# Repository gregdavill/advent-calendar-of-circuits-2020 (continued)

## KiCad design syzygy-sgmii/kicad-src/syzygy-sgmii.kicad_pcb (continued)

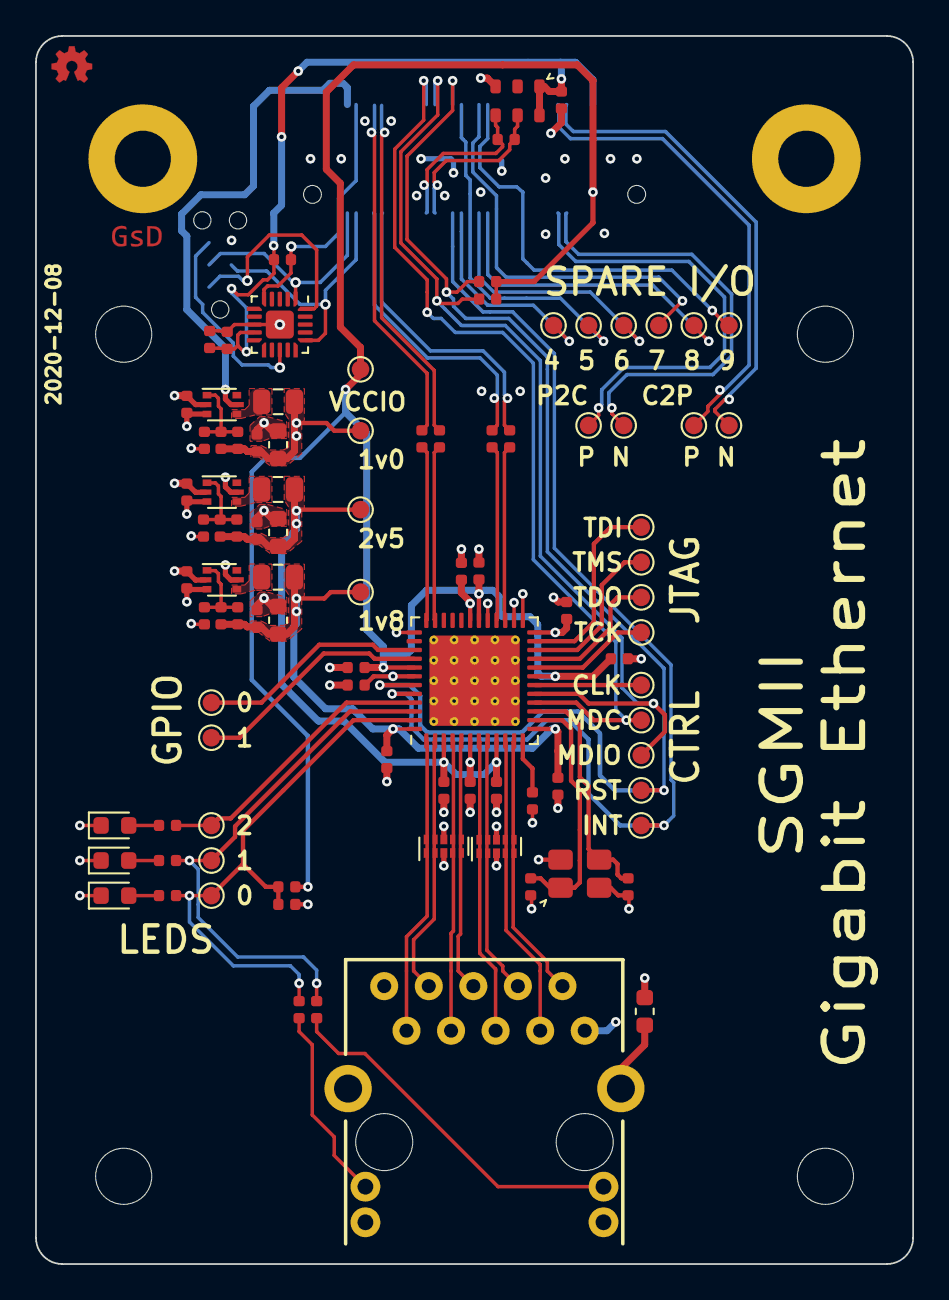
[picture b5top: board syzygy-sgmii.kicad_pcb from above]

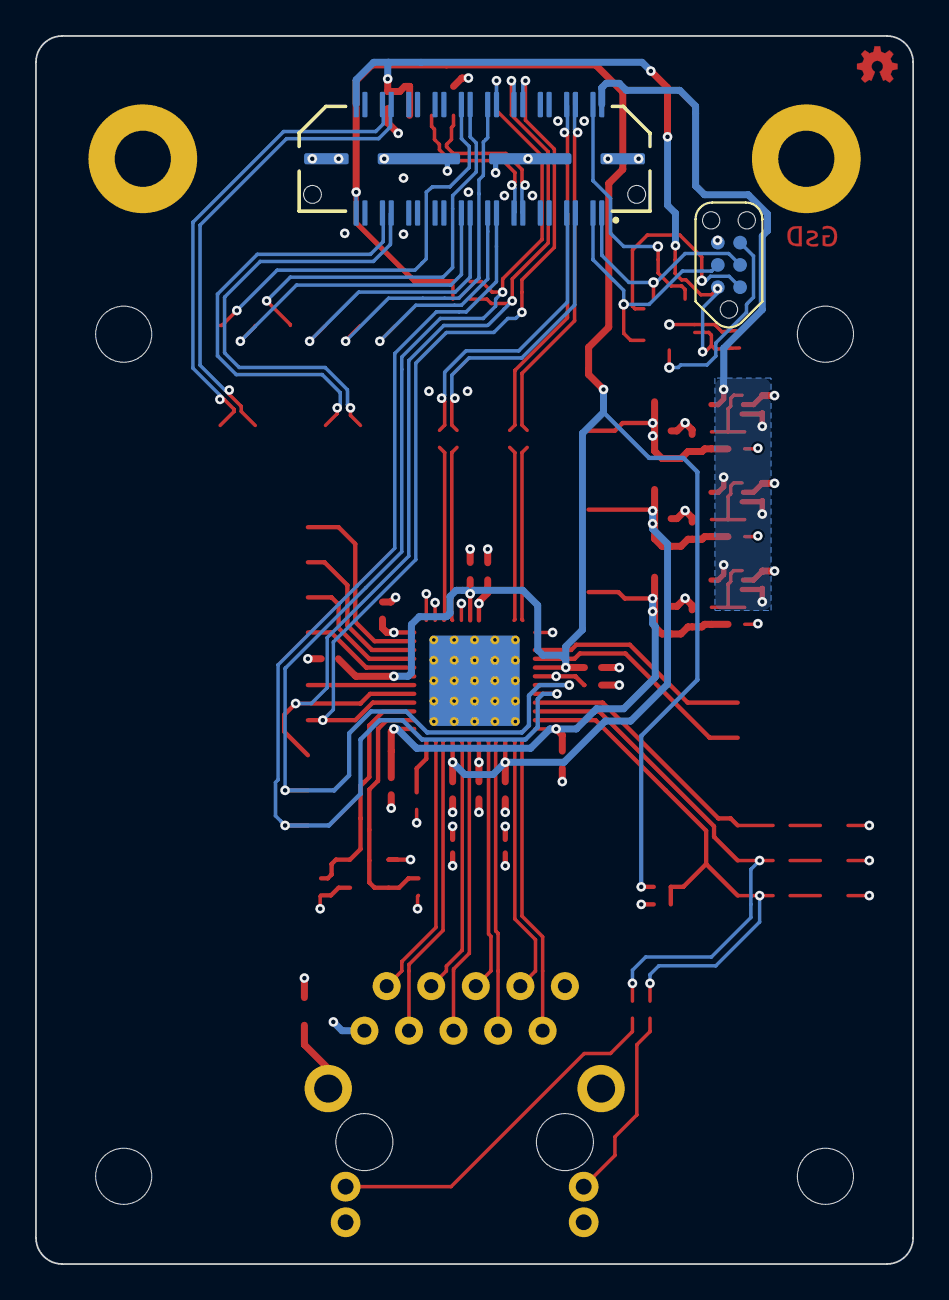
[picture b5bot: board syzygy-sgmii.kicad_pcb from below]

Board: 4 copper layers, 50.0 x 70.0 mm, 101 parts (2 on the bottom side), 69 nets.

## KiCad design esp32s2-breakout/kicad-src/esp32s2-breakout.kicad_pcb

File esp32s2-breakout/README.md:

# ESP32s2 Breakout

---

## What is it

ESP32S2 + Sharp memory LCD + prototyping area

## Folder structure

```
kicad-src: KiCad v6 source files
production:
 - Gerbers:      [project]_gerbers.zip
 - Schematic:    [project].pdf
 - Board render: [project].png
```

## Render

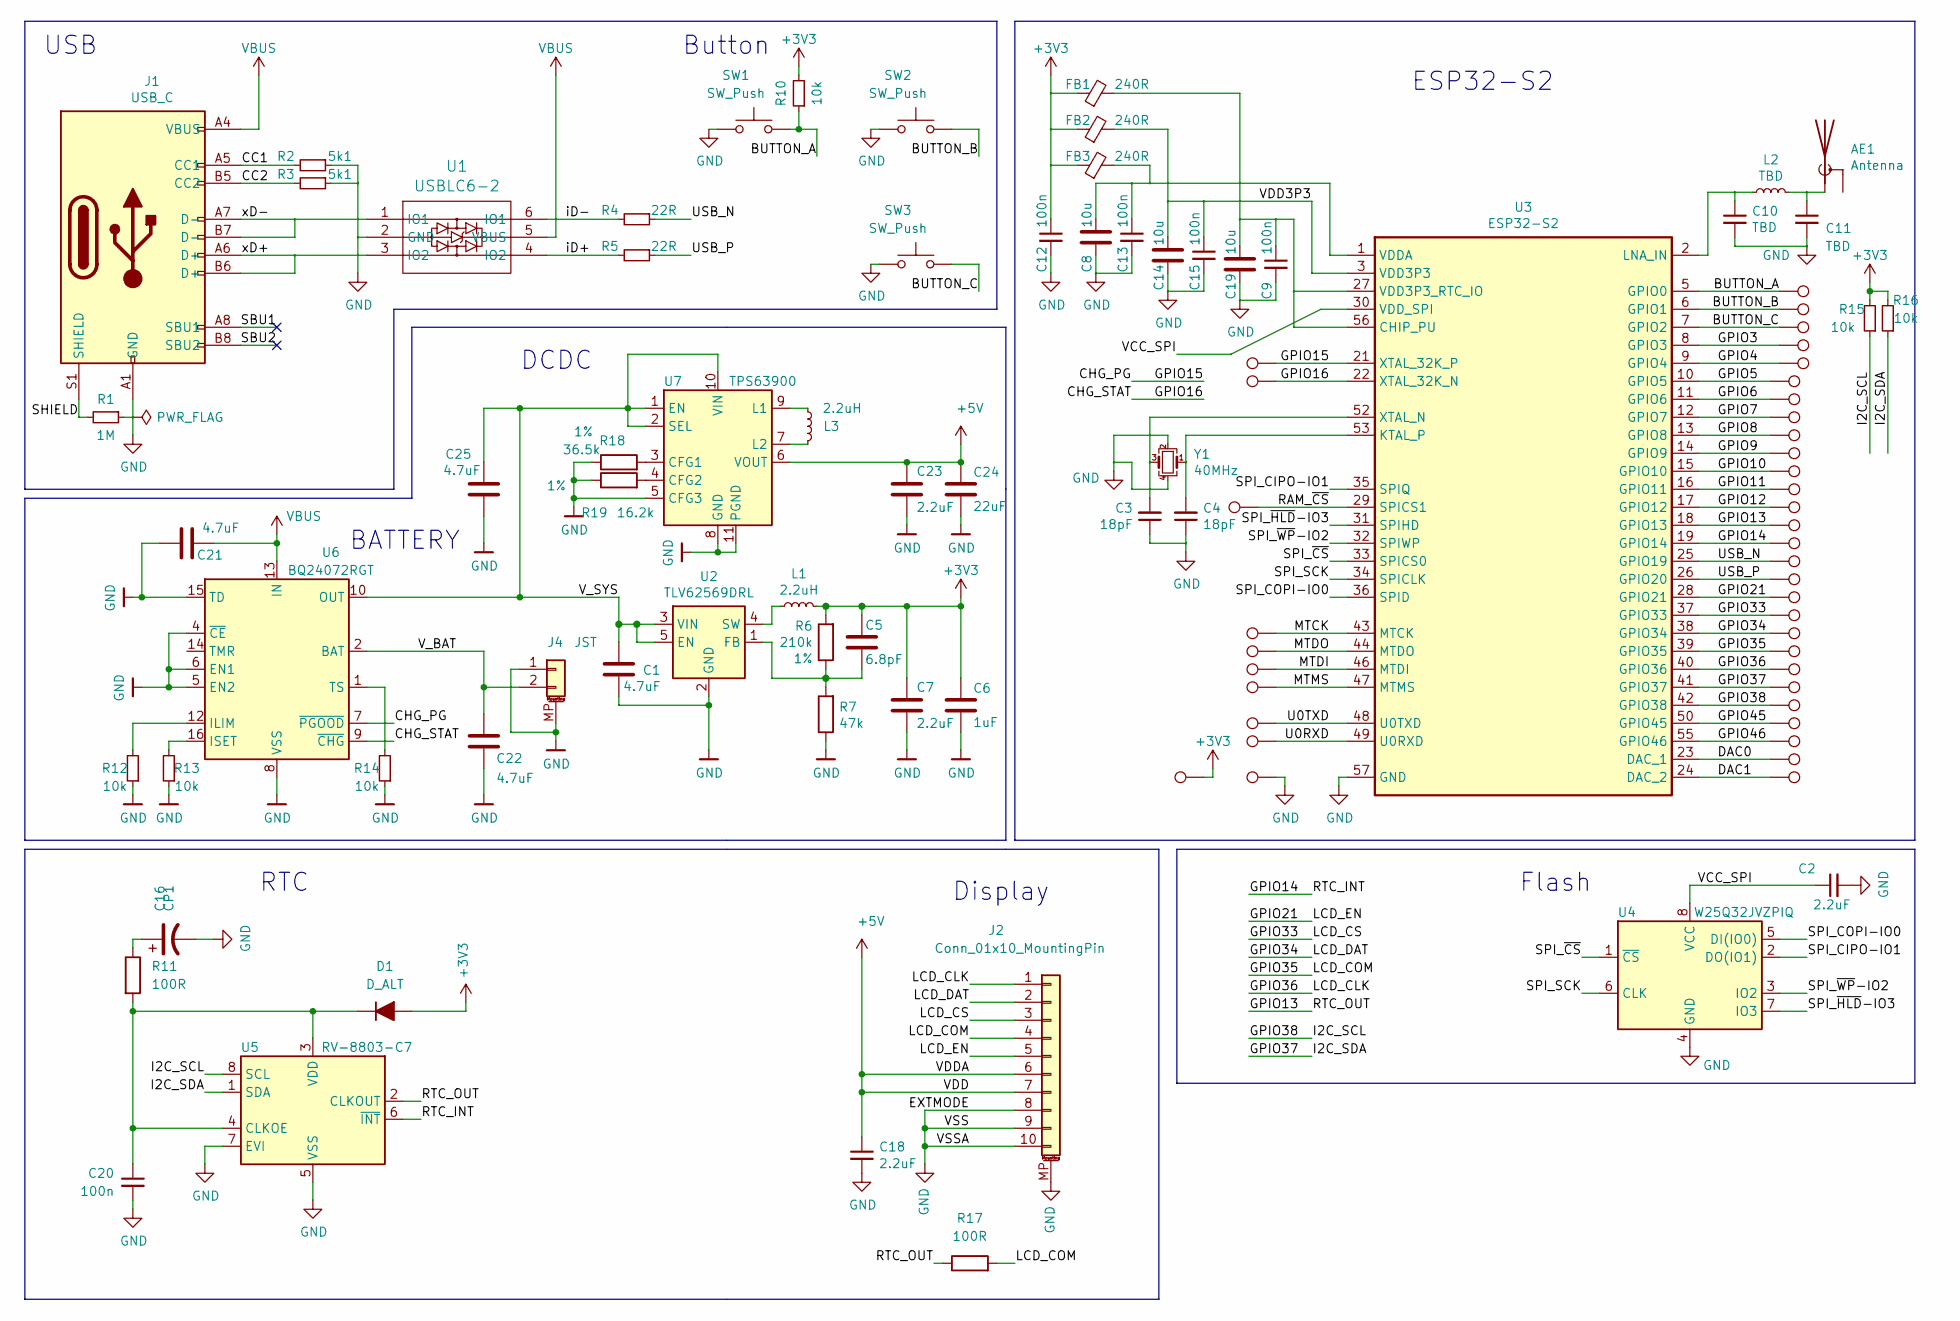
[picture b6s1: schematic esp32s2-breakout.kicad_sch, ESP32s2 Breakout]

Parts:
AE1: Antenna; Ant_3216
C1, C21, C22, C25: 4.7uF; C_0402_1005Metric
C2, C7, C18, C23: 2.2uF; C_0402_1005Metric
C3, C4: 18pF; C_0402_1005Metric
C5: 6.8pF; C_0402_1005Metric
C6: 1uF; C_0402_1005Metric
C8, C14, C19: 10u; C_0603_1608Metric
C9, C12, C13, C15, C20: 100n; C_0402_1005Metric
C10, C11: TBD; C_0402_1005Metric
C16: CP1; BatteryHolder_Seiko_MS621F
C24: 22uF; C_0603_1608Metric
D1: D_ALT; D_SOD-523
FB1, FB2, FB3: 240R; L_0402_1005Metric
J1: USB_C; USB_C_Receptacle_HRO_TYPE-C-31-M-12
J2: Conn_01x10_MountingPin; Hirose_FH33-10S-0.5SH_1x10-1MP_P0.50mm_Horizontal
J4: JST; BM02B-GHS-TBT
L1, L3: 2.2uH; L_0805_2012Metric
L2: TBD; L_0402_1005Metric
R1: 1M; R_0402_1005Metric
R2, R3: 5k1; R_0402_1005Metric
R4, R5: 22R; R_0402_1005Metric
R6: 210k; R_0402_1005Metric
R7: 47k; R_0402_1005Metric
R10, R12, R13, R14, R15, R16: 10k; R_0402_1005Metric
R11, R17: 100R; R_0402_1005Metric
R18: 36.5k; R_0402_1005Metric
R19: 16.2k; R_0402_1005Metric
SW1, SW2, SW3: SW_Push; SW_SPST_PTS810
TP1, TP2, TP3, TP4, TP5, TP6, TP7, TP8, TP9, TP10, TP11, TP12, TP13, TP14, TP15, TP16, TP17, TP18, TP19, TP20, TP21, TP22, TP23, TP24, TP25, TP26, TP27, TP28, TP29, TP30, TP31, TP32, TP33, TP34, TP35, TP36, TP37, TP38, TP39: TestPoint; TestPoint_Pad_1.0x1.0mm
U1: USBLC6-2; SOT-666
U2: TLV62569DRL; SOT-666
U3: ESP32-S2; QFN-56-1EP_7x7mm_P0.4mm_EP5.6x5.6mm
U4: W25Q32JVZPIQ; WSON-8-1EP_6x5mm_P1.27mm_EP3.4x4mm
U5: RV-8803-C7; RTC_SMD_MicroCrystal_C3_2.5x3.7mm
U6: BQ24072RGT; VQFN-16-1EP_3x3mm_P0.5mm_EP1.6x1.6mm
U7: TPS63900; WSON-10-1EP_2.5x2.5mm_P0.5mm_EP1.2x2mm_ThermalVias
Y1: 40MHz; Crystal_SMD_4Pin_2.0x1.6mm

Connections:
+3V3: C5.1, C6.1, C7.1, C12.1, D1.2 (A), FB1.1, FB2.1, FB3.1, L1.2, R6.2, R10.2, R15.2, R16.2, TP39.1; also elsewhere on the board
+5V: C18.1, C23.1, C24.1, J2.6, J2.7, U7.6 (VOUT)
/BUTTON_A: R10.1, SW1.2, TP35.1, U3.5 (GPIO0)
/BUTTON_B: SW2.2, TP36.1, U3.6 (GPIO1)
/BUTTON_C: SW3.2, TP37.1, U3.7 (GPIO2)
/CC1: J1.A5 (CC1), R2.2
/CC2: J1.B5 (CC2), R3.2
/DAC0: TP31.1, U3.23 (DAC_1)
/DAC1: TP32.1, U3.24 (DAC_2)
/GPIO3: TP9.1, U3.8 (GPIO3)
/GPIO4: TP8.1, U3.9 (GPIO4)
/GPIO5: TP10.1, U3.10 (GPIO5)
/GPIO6: TP11.1, U3.11 (GPIO6)
/GPIO7: TP12.1, U3.12 (GPIO7)
/GPIO8: TP13.1, U3.13 (GPIO8)
/GPIO9: TP14.1, U3.14 (GPIO9)
/GPIO10: TP15.1, U3.15 (GPIO10)
/GPIO11: TP16.1, U3.16 (GPIO11)
/GPIO12: TP17.1, U3.17 (GPIO12)
/GPIO14: TP19.1, U3.19 (GPIO14), U5.6 (~INT)
/GPIO15: TP33.1, U3.21 (XTAL_32K_P), U6.7 (~PGOOD)
/GPIO16: TP34.1, U3.22 (XTAL_32K_N), U6.9 (~CHG)
/GPIO21: J2.5, TP22.1, U3.28 (GPIO21)
/GPIO33: J2.3, TP23.1, U3.37 (GPIO33)
/GPIO34: J2.2, TP24.1, U3.38 (GPIO34)
/GPIO35: J2.4, R17.2, TP25.1, U3.39 (GPIO35)
/GPIO36: J2.1, TP26.1, U3.40 (GPIO36)
/GPIO37: R16.1, TP27.1, U3.41 (GPIO37), U5.1 (SDA)
/GPIO38: R15.1, TP28.1, U3.42 (GPIO38), U5.8 (SCL)
/GPIO45: TP29.1, U3.50 (GPIO45)
/GPIO46: TP30.1, U3.55 (GPIO46)
/MTCK: TP1.1, U3.43 (MTCK)
/MTDI: TP3.1, U3.46 (MTDI)
/MTDO: TP2.1, U3.44 (MTDO)
/MTMS: TP4.1, U3.47 (MTMS)
/RAM_~CS: TP38.1, U3.29 (SPICS1)
/RTC_OUT: R17.1, TP18.1, U3.18 (GPIO13), U5.2 (CLKOUT)
/SBU1: J1.A8 (SBU1)
/SBU2: J1.B8 (SBU2)
/SHIELD: J1.S1 (SHIELD), R1.2
/SPI_CIPO-IO1: U3.35 (SPIQ), U4.2 (DO(IO1))
/SPI_COPI-IO0: U3.36 (SPID), U4.5 (DI(IO0))
/SPI_SCK: U3.34 (SPICLK), U4.6 (CLK)
/SPI_~CS: U3.33 (SPICS0), U4.1 (~CS)
/SPI_~HLD~-IO3: U3.31 (SPIHD), U4.7 (IO3)
/SPI_~WP~-IO2: U3.32 (SPIWP), U4.3 (IO2)
/U0RXD: TP6.1, U3.49 (U0RXD)
/U0TXD: TP5.1, U3.48 (U0TXD)
/USB_N: R4.1, TP20.1, U3.25 (GPIO19)
/USB_P: R5.1, TP21.1, U3.26 (GPIO20)
/VCC_SPI: C2.1, U3.30 (VDD_SPI), U4.8 (VCC)
/VDD3P3: C14.1, C15.1, FB2.2, U3.3 (VDD3P3), U3.4 (VDD3P3)
/V_BAT: C22.2, J4.2, U6.2 (BAT), U6.3 (BAT)
/V_SYS: C1.1, C25.1, U2.3 (VIN), U2.5 (EN), U6.10 (OUT), U6.11 (OUT), U7.1 (EN), U7.2 (SEL), U7.10 (VIN)
/iD+: R5.2, U1.4 (IO2)
/iD-: R4.2, U1.6 (IO1)
/xD+: J1.A6 (D+), J1.B6 (D+), U1.3 (IO2)
/xD-: J1.A7 (D-), J1.B7 (D-), U1.1 (IO1)
GND: C1.2, C2.2, C3.1, C4.1, C6.2, C7.2, C8.2, C9.2, C10.2, C11.2, C12.2, C13.2, C14.2, C15.2, C16.2, C18.2, C19.2, C20.2, C21.1, C22.1, C23.2, C24.2, C25.2, J1.A1 (GND), J1.A12 (GND), J1.B1 (GND), J1.B12 (GND), J2.8, J2.9, J2.10, J2.MP (MountPin), J4.1, J4.MP (MountPin), R1.1, R2.1, R3.1, R7.1, R12.1, R13.1, R14.1, R18.1, R19.1, SW1.1, SW2.1, SW3.1, TP7.1, U1.2 (GND), U2.2 (GND), U3.57 (GND), U4.4 (GND), U5.5 (VSS), U5.7 (EVI), U6.4 (~CE), U6.5 (EN2), U6.6 (EN1), U6.8 (VSS), U6.15 (TD), U6.17 (VSS), U7.5 (CFG3), U7.8 (GND), U7.11 (PGND), Y1.2, Y1.4; also elsewhere on the board
unnamed: AE1.1 (A), C11.1, L2.2
unnamed: C3.2, U3.52 (XTAL_N), Y1.3
unnamed: C4.2, U3.53 (KTAL_P), Y1.1
unnamed: C5.2, R6.1, R7.2, U2.1 (FB)
unnamed: C10.1, L2.1, U3.2 (LNA_IN)
unnamed: C8.1, C13.1, FB3.2, U3.1 (VDDA), U3.51 (VDDA), U3.54 (VDDA)
unnamed: C16.1, R11.1
unnamed: C9.1, C19.1, FB1.2, U3.20 (VDD3P3_RTC), U3.27 (VDD3P3_RTC_IO), U3.45 (VDD3P3_CPU), U3.56 (CHIP_PU)
unnamed: C20.1, D1.1 (K), R11.2, U5.3 (VDD), U5.4 (CLKOE)
unnamed: L1.1, U2.4 (SW)
unnamed: L3.1, U7.9 (L1)
unnamed: L3.2, U7.7 (L2)
unnamed: R12.2, U6.12 (ILIM)
unnamed: R13.2, U6.16 (ISET)
unnamed: R14.2, U6.1 (TS)
unnamed: R18.2, U7.3 (CFG1)
unnamed: R19.2, U7.4 (CFG2)
VBUS: C21.2, J1.A4 (VBUS), J1.A9 (VBUS), J1.B4 (VBUS), J1.B9 (VBUS), U1.5 (VBUS), U6.13 (IN)

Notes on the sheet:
USB
RTC
BATTERY
DCDC
Button
Display
ESP32-S2
Flash

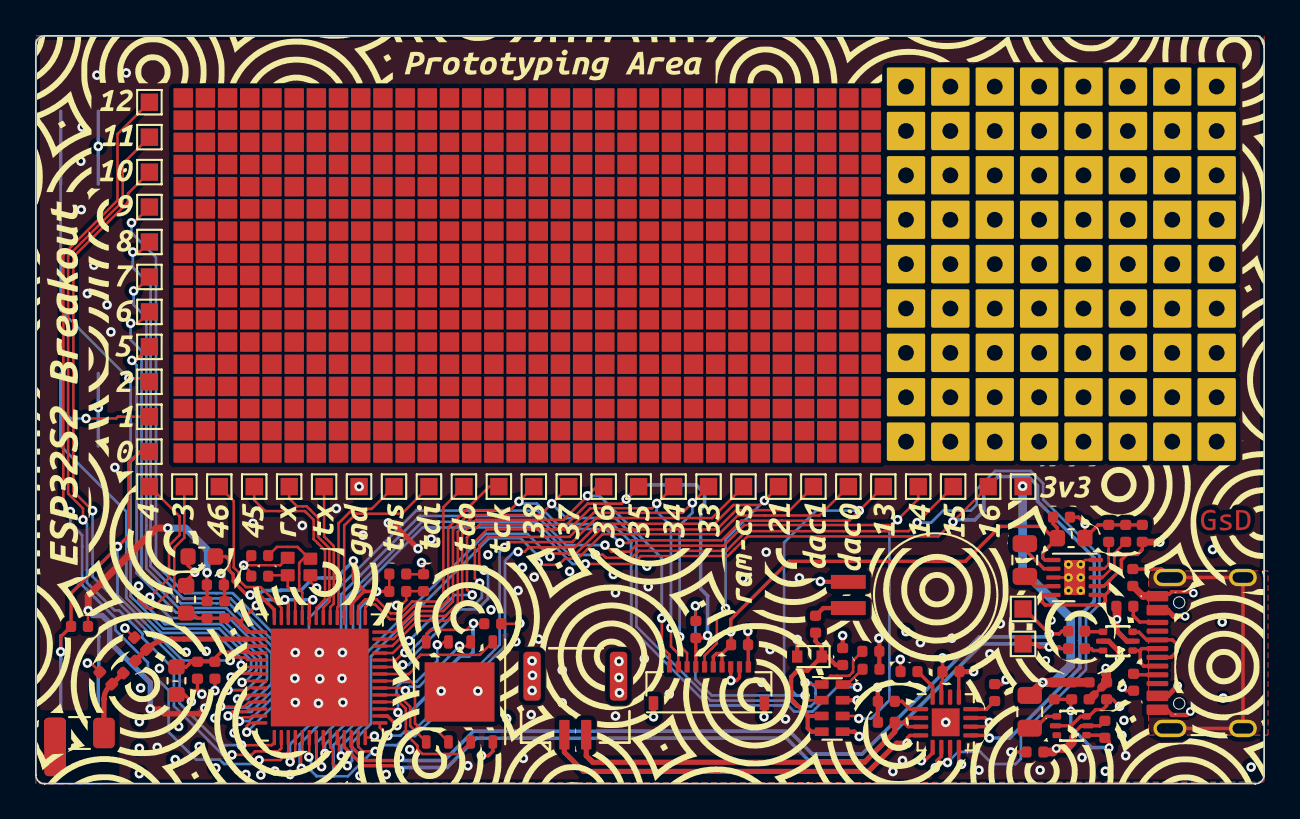
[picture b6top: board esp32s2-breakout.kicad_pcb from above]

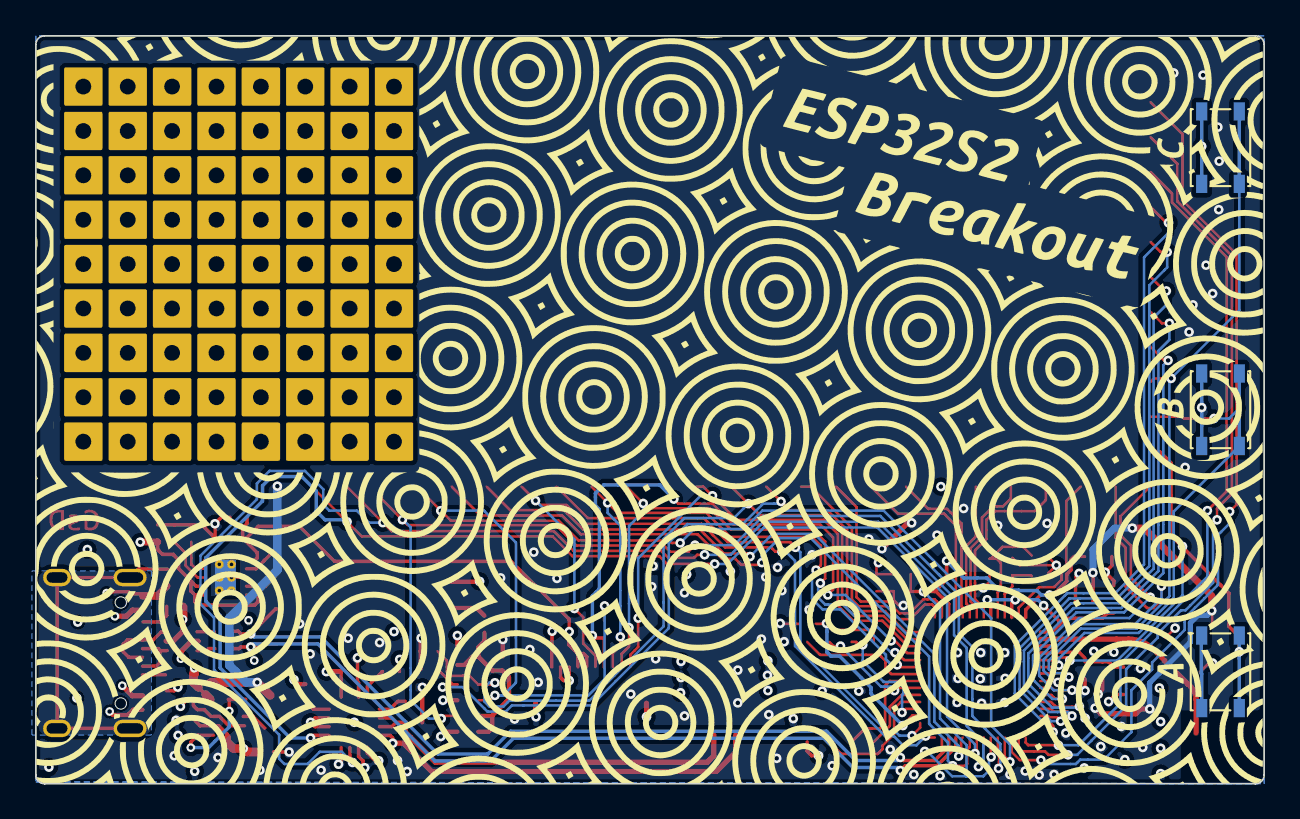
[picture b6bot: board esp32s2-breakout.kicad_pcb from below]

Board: 4 copper layers, 70.3 x 42.8 mm, 103 parts (3 on the bottom side), 75 nets.

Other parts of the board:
C17: 2.2uF; C_0402_1005Metric

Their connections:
+3V3: C17.1; also elsewhere on the board
GND: C17.2; also elsewhere on the board

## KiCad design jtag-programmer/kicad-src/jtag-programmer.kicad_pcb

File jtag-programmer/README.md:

# FT232H based JTAG programmer

## What is it

Yet Another FT232H based JTAG programmer

## Folder structure

```
kicad-src: KiCad v6 source files
production:
 - Gerbers:      [project]_gerbers.zip
 - Schematic:    [project].pdf
 - Board render: [project].png
```

## Render

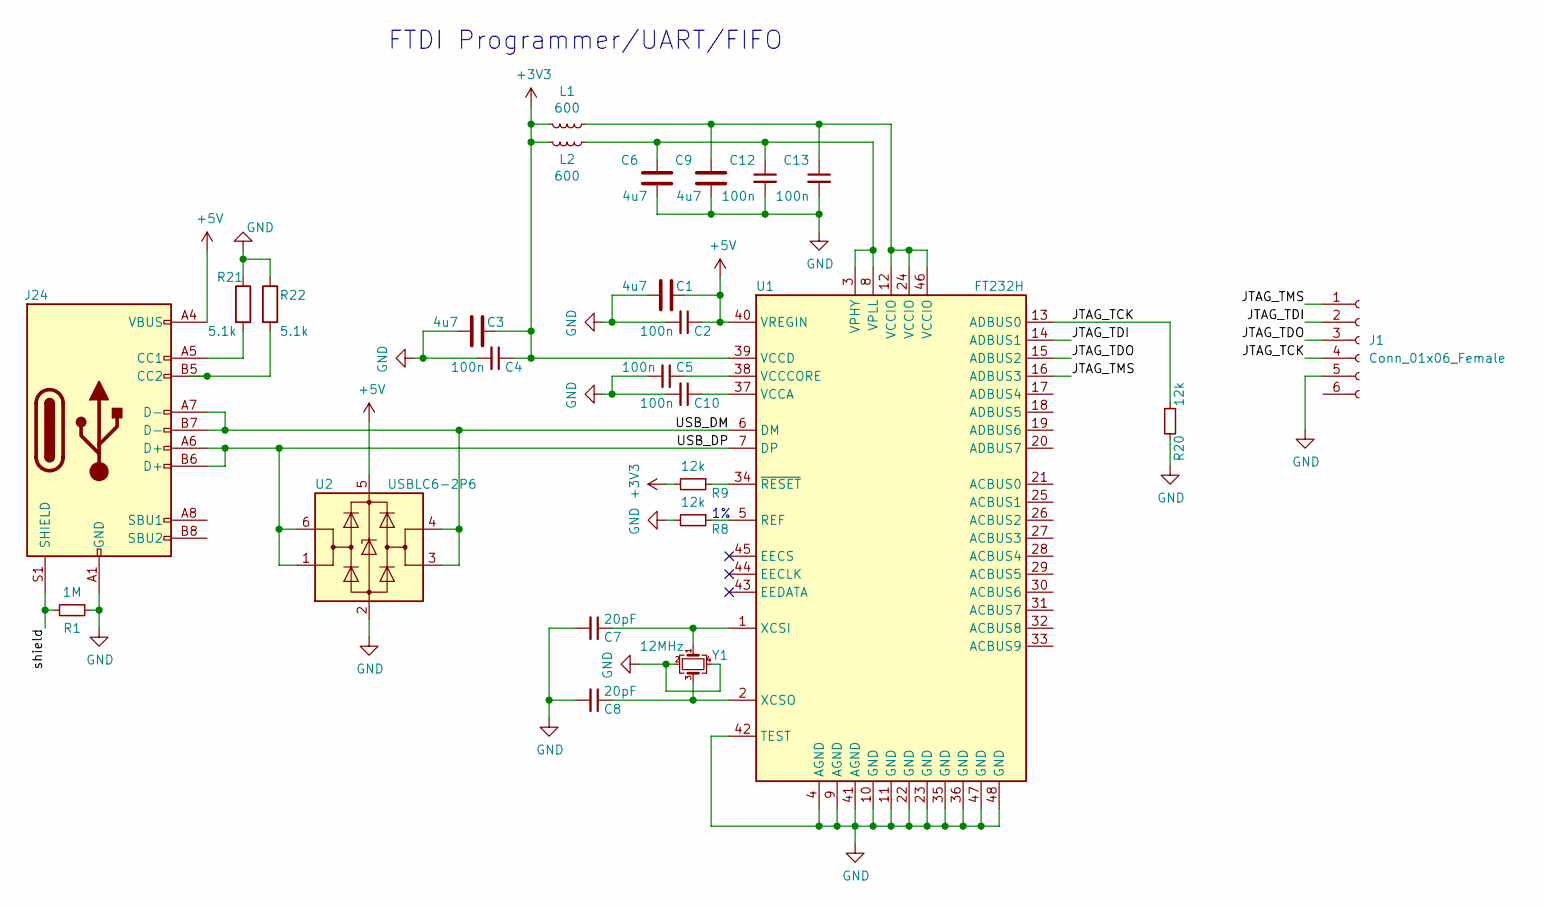
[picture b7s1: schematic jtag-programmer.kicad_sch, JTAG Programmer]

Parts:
C1, C3, C6, C9: 4u7; C_0603_1608Metric
C2, C4, C5, C10, C12, C13: 100n; C_0402_1005Metric
C7, C8: 20pF; C_0402_1005Metric
J1: Conn_01x06_Female; PinSocket_1x06_P2.54mm_Horizontal
J24: USB_C_Receptacle_USB2.0; USB_C_Receptacle_HRO_TYPE-C-31-M-12
L1, L2: 600; L_0402_1005Metric
R1: 1M; R_0402_1005Metric
R8, R9, R20: 12k; R_0402_1005Metric
R21, R22: 5.1k; R_0402_1005Metric
U1: FT232H; QFN-48-1EP_8x8mm_P0.5mm_EP6.2x6.2mm
U2: USBLC6-2P6; SOT-666
Y1: 12MHz; Crystal_SMD_3225-4Pin_3.2x2.5mm

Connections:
+3V3: C3.1, C4.1, L1.1, L2.1, R9.2, U1.39 (VCCD)
+5V: C1.1, C2.1, J24.A4 (VBUS), J24.A9 (VBUS), J24.B4 (VBUS), J24.B9 (VBUS), U1.40 (VREGIN), U2.5 (VBUS)
/JTAG_TCK: J1.4, R20.1, U1.13 (ADBUS0)
/JTAG_TDI: J1.2, U1.14 (ADBUS1)
/JTAG_TDO: J1.3, U1.15 (ADBUS2)
/JTAG_TMS: J1.1, U1.16 (ADBUS3)
/USB_DM: J24.A7 (D-), J24.B7 (D-), U1.6 (DM), U2.3 (I/O2), U2.4 (I/O2)
/USB_DP: J24.A6 (D+), J24.B6 (D+), U1.7 (DP), U2.1 (I/O1), U2.6 (I/O1)
/shield: J24.S1 (SHIELD), R1.2
GND: C1.2, C2.2, C3.2, C4.2, C5.2, C6.2, C7.2, C8.2, C9.2, C10.2, C12.2, C13.2, J1.5, J24.A1 (GND), J24.A12 (GND), J24.B1 (GND), J24.B12 (GND), R1.1, R8.2, R20.2, R21.1, R22.1, U1.4 (AGND), U1.9 (AGND), U1.10 (GND), U1.11 (GND), U1.22 (GND), U1.23 (GND), U1.35 (GND), U1.36 (GND), U1.41 (AGND), U1.42 (TEST), U1.47 (GND), U1.48 (GND), U1.49, U2.2 (GND), Y1.2, Y1.4
unnamed: C5.1, U1.38 (VCCCORE)
unnamed: C7.1, U1.1 (XCSI), Y1.1
unnamed: C8.1, U1.2 (XCSO), Y1.3
unnamed: C10.1, U1.37 (VCCA)
unnamed: C6.1, C12.1, L2.2, U1.3 (VPHY), U1.8 (VPLL)
unnamed: C9.1, C13.1, L1.2, U1.12 (VCCIO), U1.24 (VCCIO), U1.46 (VCCIO)
unnamed: J24.A5 (CC1), R21.2
unnamed: J24.B5 (CC2), R22.2
unnamed: R8.1, U1.5 (REF)
unnamed: R9.1, U1.34 (~RESET)
no_connect_38: U1.43 (EEDATA)
no_connect_39: U1.44 (EECLK)
no_connect_40: U1.45 (EECS)

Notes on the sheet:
FTDI Programmer/UART/FIFO

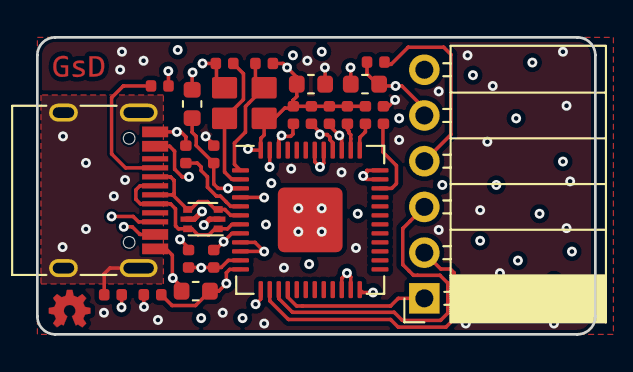
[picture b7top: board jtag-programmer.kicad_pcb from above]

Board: 4 copper layers, 31.0 x 16.5 mm, 25 parts (0 on the bottom side), 20 nets.

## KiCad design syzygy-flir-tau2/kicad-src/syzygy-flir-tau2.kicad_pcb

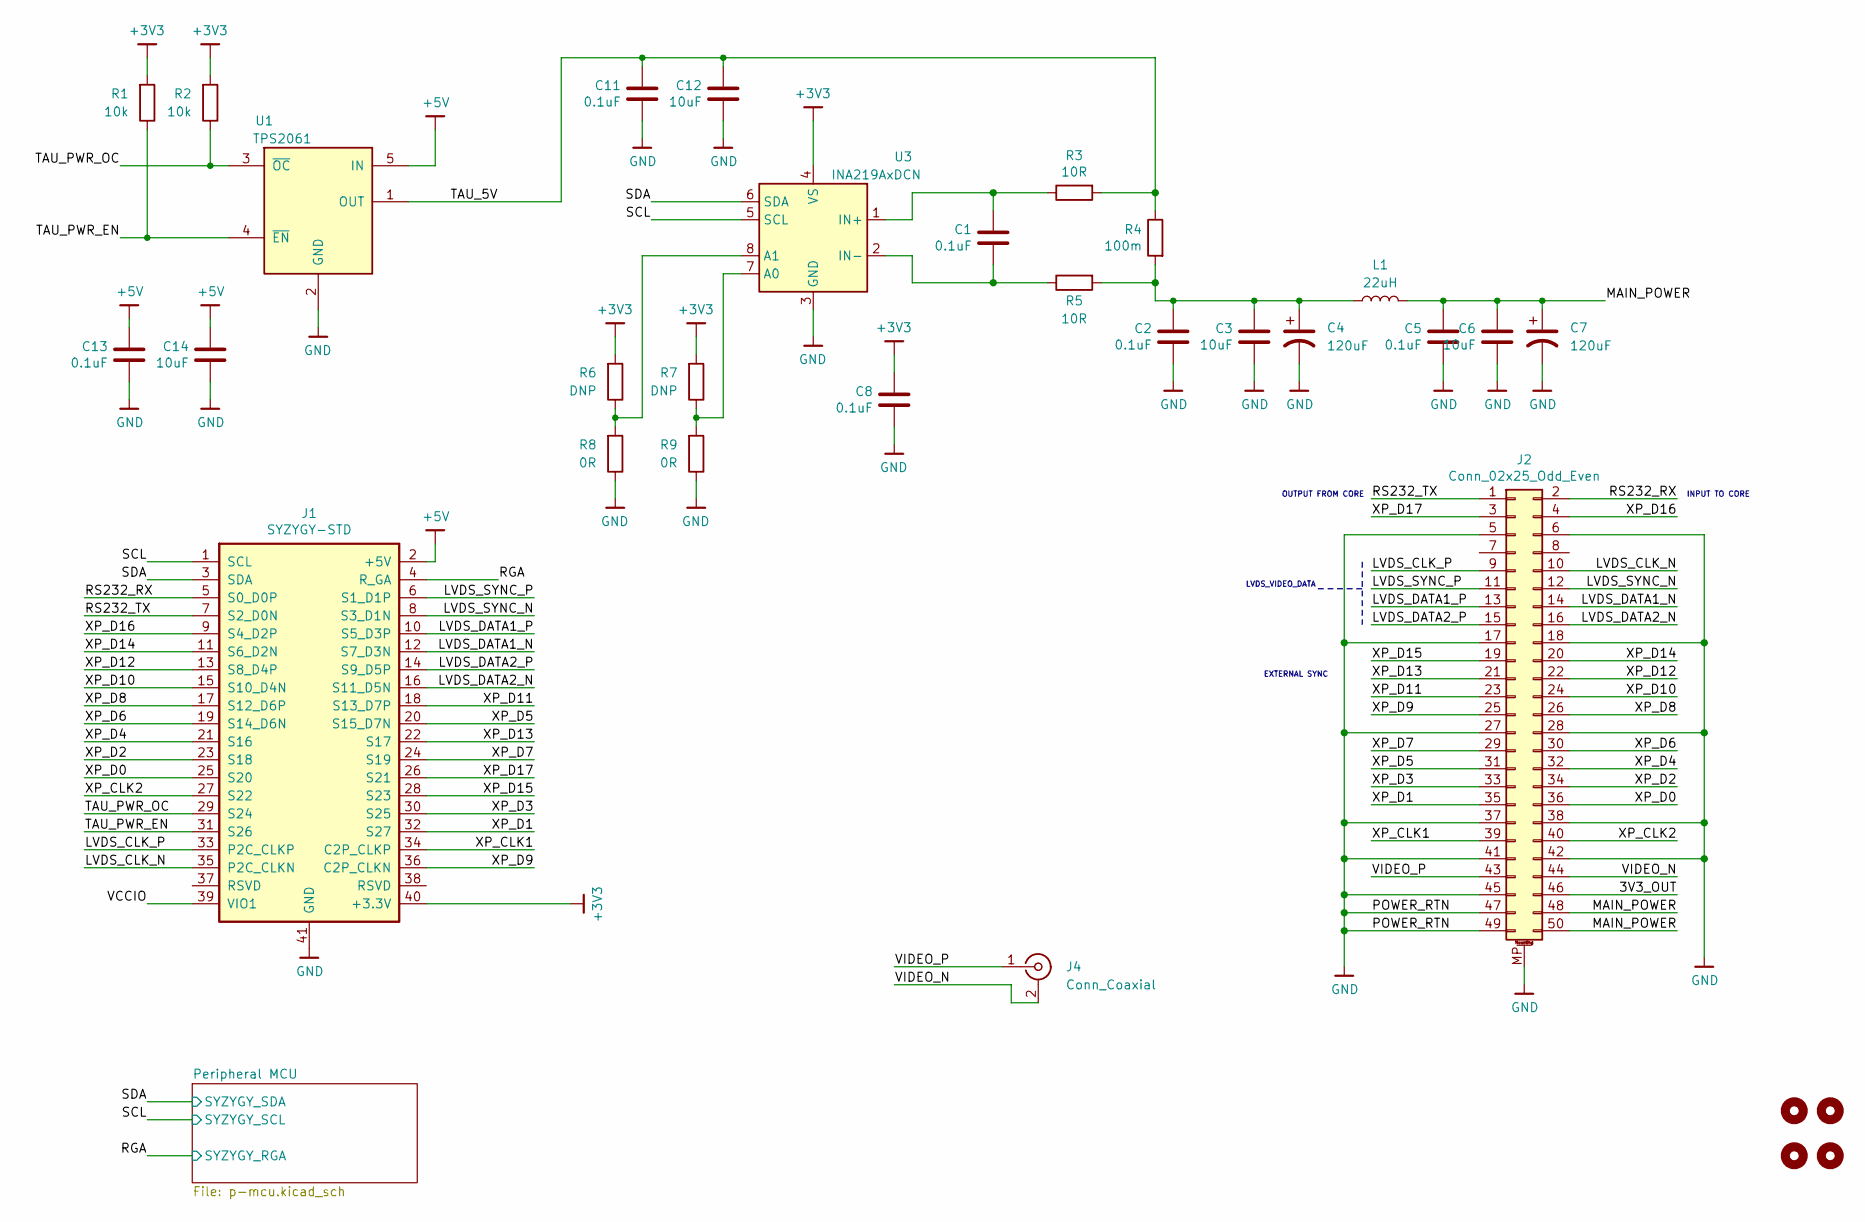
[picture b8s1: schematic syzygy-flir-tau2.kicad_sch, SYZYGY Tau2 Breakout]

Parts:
C1, C2, C5, C8, C11, C13: 0.1uF; C_0402_1005Metric
C3, C6, C12, C14: 10uF; C_0805_2012Metric
C4, C7: 120uF; CP_Elec_6.3x5.3
H1, H2, H3, H4: MountingHole; MountingHole_3.2mm_M3_DIN965
J1: SYZYGY-STD; SYZYGY-STD-POD
J2: Conn_02x25_Odd_Even; DF12(5.0)-50DP
J4: Conn_Coaxial; MMCX_Molex_73415-1471_Vertical
L1: 22uH; L_Taiyo-Yuden_NR-50xx
R1, R2: 10k; R_0402_1005Metric
R3, R5: 10R; R_0402_1005Metric
R4: 100m; R_0805_2012Metric
R6, R7: DNP; R_0402_1005Metric
R8, R9: 0R; R_0402_1005Metric
U1: TPS2061; SOT-23-5
U3: INA219AxDCN; SOT-23-8

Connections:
+3V3: C8.1, J1.40 (+3.3V), R1.2, R2.2, R6.2, R7.2, U3.4 (VS); also elsewhere on the board
+5V: C13.1, C14.1, J1.2 (+5V), U1.5 (IN)
/3V3_OUT: J2.46
/LVDS_CLK_N: J1.35 (P2C_CLKN), J2.10
/LVDS_CLK_P: J1.33 (P2C_CLKP), J2.9
/LVDS_DATA1_N: J1.12 (S7_D3N), J2.14
/LVDS_DATA1_P: J1.10 (S5_D3P), J2.13
/LVDS_DATA2_N: J1.16 (S11_D5N), J2.16
/LVDS_DATA2_P: J1.14 (S9_D5P), J2.15
/LVDS_SYNC_N: J1.8 (S3_D1N), J2.12
/LVDS_SYNC_P: J1.6 (S1_D1P), J2.11
/MAIN_POWER: C5.1, C6.1, C7.1, J2.48, J2.50, L1.2
/RGA: J1.4 (R_GA); also elsewhere on the board
/RS232_RX: J1.5 (S0_D0P), J2.2
/RS232_TX: J1.7 (S2_D0N), J2.1
/SCL: J1.1 (SCL), U3.5 (SCL); also elsewhere on the board
/SDA: J1.3 (SDA), U3.6 (SDA); also elsewhere on the board
/TAU_5V: C11.1, C12.1, R3.2, R4.1, U1.1 (OUT)
/TAU_PWR_EN: J1.31 (S26), R1.1, U1.4 (~EN)
/TAU_PWR_OC: J1.29 (S24), R2.1, U1.3 (~OC)
/VCCIO: J1.39 (VIO1)
/VIDEO_N: J2.44, J4.2 (Ext)
/VIDEO_P: J2.43, J4.1 (In)
/XP_CLK1: J1.34 (C2P_CLKP), J2.39
/XP_CLK2: J1.27 (S22), J2.40
/XP_D0: J1.25 (S20), J2.36
/XP_D1: J1.32 (S27), J2.35
/XP_D2: J1.23 (S18), J2.34
/XP_D3: J1.30 (S25), J2.33
/XP_D4: J1.21 (S16), J2.32
/XP_D5: J1.20 (S15_D7N), J2.31
/XP_D6: J1.19 (S14_D6N), J2.30
/XP_D7: J1.24 (S19), J2.29
/XP_D8: J1.17 (S12_D6P), J2.26
/XP_D9: J1.36 (C2P_CLKN), J2.25
/XP_D10: J1.15 (S10_D4N), J2.24
/XP_D11: J1.18 (S13_D7P), J2.23
/XP_D12: J1.13 (S8_D4P), J2.22
/XP_D13: J1.22 (S17), J2.21
/XP_D14: J1.11 (S6_D2N), J2.20
/XP_D15: J1.28 (S23), J2.19
/XP_D16: J1.9 (S4_D2P), J2.4
/XP_D17: J1.26 (S21), J2.3
GND: C2.2, C3.2, C4.2, C5.2, C6.2, C7.2, C8.2, C11.2, C12.2, C13.2, C14.2, J1.41 (GND), J2.5, J2.6, J2.17, J2.18, J2.27, J2.28, J2.37, J2.38, J2.41, J2.42, J2.45, J2.47, J2.49, J2.MP (MountPin), R8.1, R9.1, U1.2 (GND), U3.3 (GND); also elsewhere on the board
unnamed: C1.1, R3.1, U3.1 (IN+)
unnamed: C1.2, R5.1, U3.2 (IN-)
unnamed: C2.1, C3.1, C4.1, L1.1, R4.2, R5.2
unnamed: R6.1, R8.2, U3.8 (A1)
unnamed: R7.1, R9.2, U3.7 (A0)

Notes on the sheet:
LVDS_VIDEO_DATA
EXTERNAL SYNC
OUTPUT FROM CORE
INPUT TO CORE

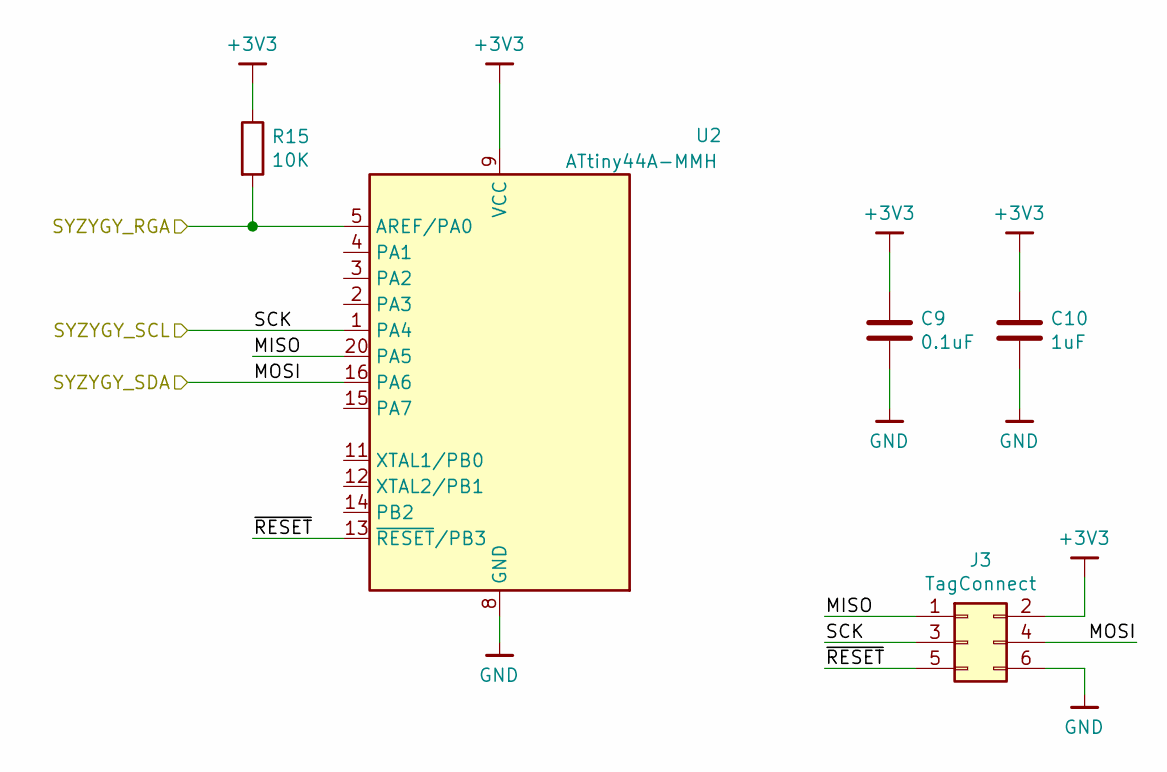
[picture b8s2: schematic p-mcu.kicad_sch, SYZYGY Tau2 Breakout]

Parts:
C9: 0.1uF; C_0402_1005Metric
C10: 1uF; C_0402_1005Metric
J3: TagConnect; TC2030-NL_SMALL
R15: 10K; R_0402_1005Metric
U2: ATtiny44A-MMH; QFN-20-1EP_3x3mm_P0.45mm_EP1.6x1.6mm

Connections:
+3V3: C9.1, C10.1, J3.2, R15.1, U2.9 (VCC); also elsewhere on the board
/Peripheral MCU/MISO: J3.1, U2.20 (PA5)
/Peripheral MCU/~RESET: J3.5, U2.13 (~RESET~/PB3)
/RGA: R15.2, U2.5 (AREF/PA0); also elsewhere on the board
/SCL: J3.3, U2.1 (PA4); also elsewhere on the board
/SDA: J3.4, U2.16 (PA6); also elsewhere on the board
GND: C9.2, C10.2, J3.6, U2.8 (GND), U2.21 (GND); also elsewhere on the board
no_connect_63: U2.10 (NC)
no_connect_64: U2.17 (NC)
no_connect_65: U2.18 (NC)
no_connect_66: U2.19 (NC)
no_connect_67: U2.6 (NC)
no_connect_68: U2.7 (NC)

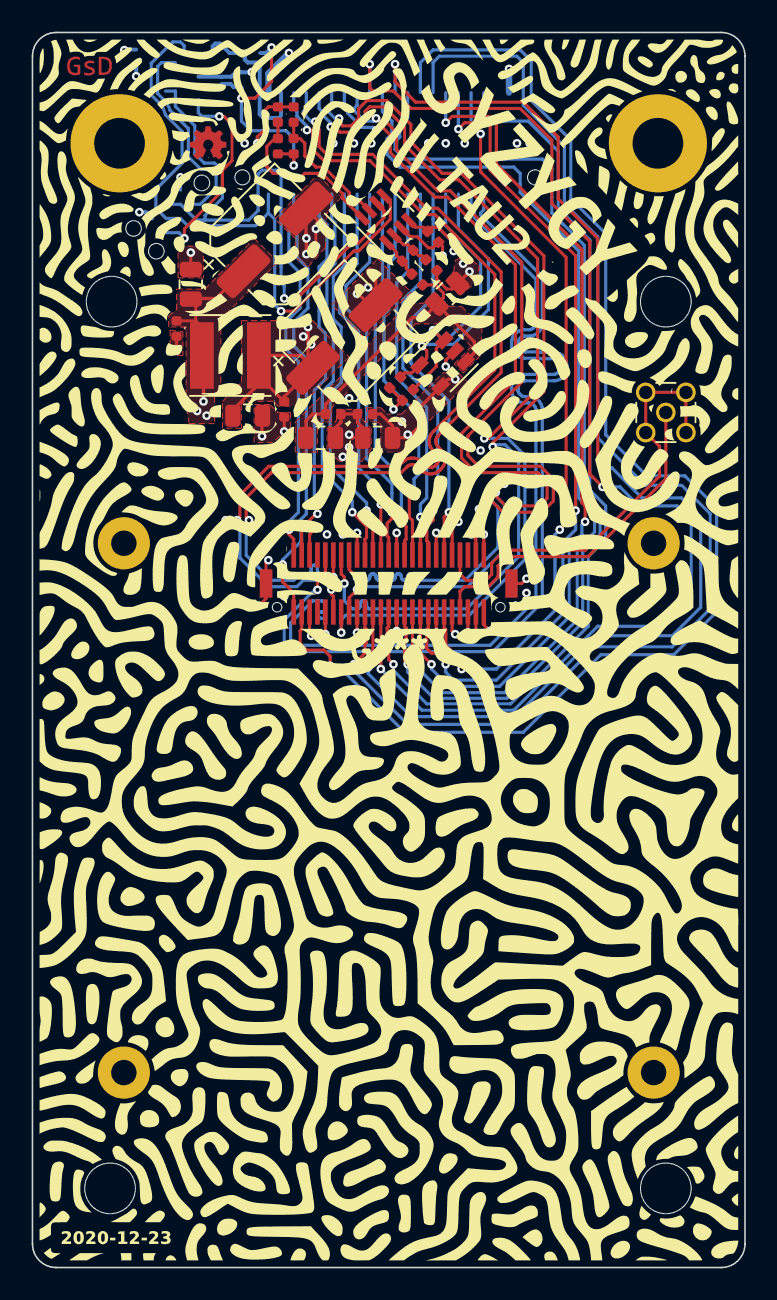
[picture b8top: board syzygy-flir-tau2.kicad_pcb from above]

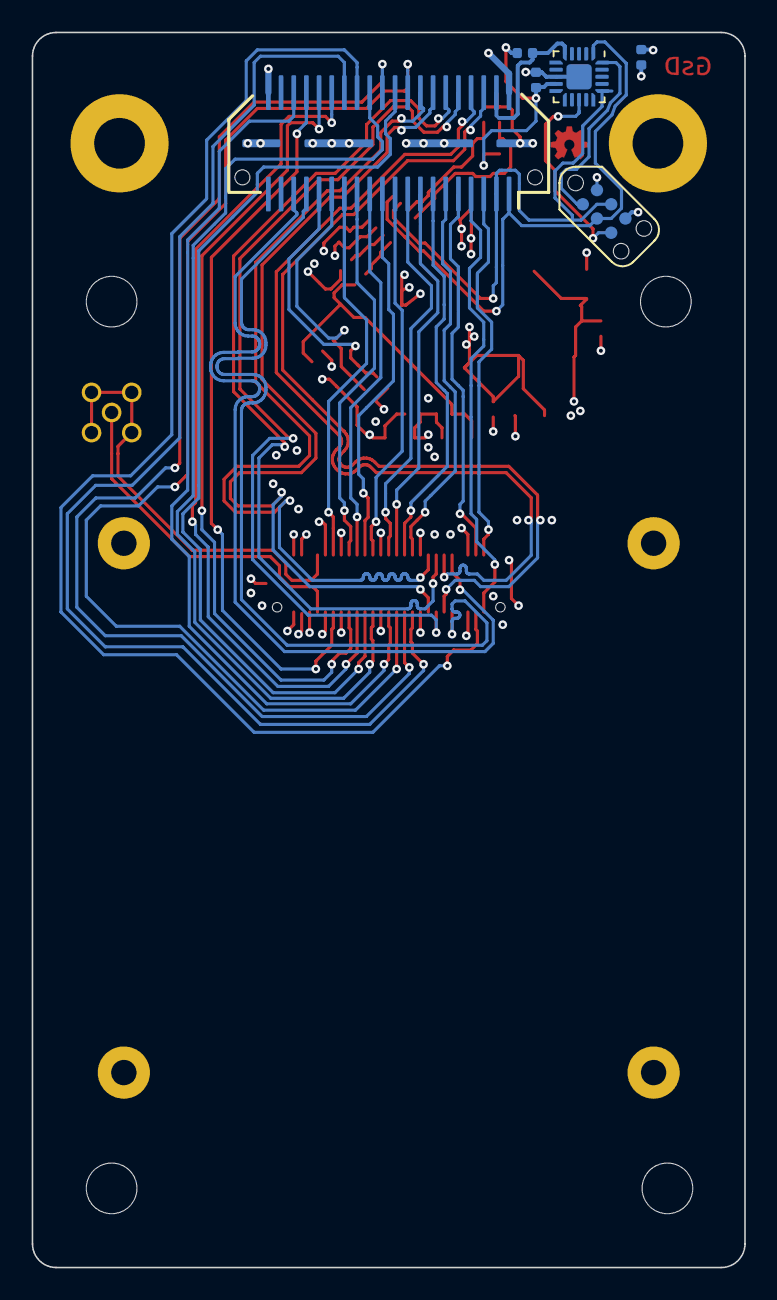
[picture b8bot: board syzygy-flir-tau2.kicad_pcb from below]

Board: 4 copper layers, 45.0 x 78.0 mm, 36 parts (6 on the bottom side), 49 nets.

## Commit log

2020-12-01 Add gpdi design
2020-12-01 Add git lfs options
2020-12-01 Add 3d models
2020-12-02 Add resonance board
2020-12-03 Add Meiji led ring
2020-12-04 Add PCIe_x4 Breakout
2020-12-05 Add icebreaker++
2020-12-06 Add PCIe x1 add-in card
2020-12-06 Add arm-watch
2020-12-06 Add readme
2020-12-06 rename arm-watch folder
2020-12-07 Add sgmii
2020-12-08 Finish syzygy-sgmii
2020-12-09 Update licence and add hdmi-si
2020-12-10 Add quad-7segment
2020-12-11 Add syzygy-breakout
2020-12-11 fix typo
2020-12-11 fix heading
2020-12-12 Add icebreaker++-ram
2020-12-13 Add sd-dummy
2020-12-14 Add gpdi serdes
2020-12-15 Add rpi-hq-camera
2020-12-16 Add syzygy-pmod
2020-12-17 Add pmod-gnss
2020-12-18 Add led-panel
2020-12-20 Add syzygy-txr
2020-12-20 add syzygy-dual-atto
2020-12-21 Added rgb888-lcd
2020-12-22 Add memory-lcd-wing
2020-12-23 Add syzygy tau2
2020-12-24 Added syzygy-boson
2020-12-25 Added SCD30
2020-12-26 Add esp32s2 co2 monitor
2020-12-26 Update esp32s2 co2 monitor
2020-12-26 esp32s2-co2-monitor: Update antenna
2020-12-26 Add jtag-programmer
2020-12-28 Added ecpbreaker
2020-12-29 Added esp32s2 lepton
2020-12-29 Added 3d models
2020-12-30 Add esp32s2-breakout
2020-12-31 Added syzygy-epc901
2021-02-05 syzygy-sgmii: Add BOM values to project
2021-02-05 ecpbreaker: Add BOM values to project
2021-02-05 syzygy-gpdi: Add BOM values to project
2021-02-05 meji-led-ring: Add BOM values to project
2021-02-05 syzygy-epc901: Add BOM values to project
2021-02-05 icebreaker++ram: Add BOM values to project
2021-02-05 libs: update
2021-02-05 syzygy-boson: Add BOM values to project
2021-06-30 move lfs files to git
